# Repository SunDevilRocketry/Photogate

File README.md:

<h1>Photogate</h1>

<p>Current PCB Revision: 1.0</p>
<p>PCB Part Number: L0004</p>

<p>The photogate board functions as an optical sensor for calibrating the absolute position of stepper motors upon controller startup (L0005). The photogate is mounted on the stepper motor adjacent to the motor shaft, which is coupled to the stem of a ball-valve used as the main propellant valve in SDR's liquid engine. The photogate uses an infrared LED to produce an optical signal on the infrared-sensitive phototransistor surface. The board has a characteristic U-shape that allows a small standoff strut on the motor coupler to block the optical path of the sensor when the valve reaches the closed position. </p>

<p><b>Working Directory Structure:</b></p>

<p>
   doc: documentation
   
   src: source design files, e.g. schematic and PCB layout files

   lib: libraries for schematic symbols and footprints

   production: files needed for pcb fabrication, e.g. gerbers, profile, drill file

   sim: simulation models/files 

   cad: 3d models
  
   img: images of circuit/footprints for github display 
</p>

<h2>3D Model: </h2>

<h2>Schematic: </h2>

<h3>Power Supply </h3>

<h3>Emitter</h3>

<h3>Sensor</h3>

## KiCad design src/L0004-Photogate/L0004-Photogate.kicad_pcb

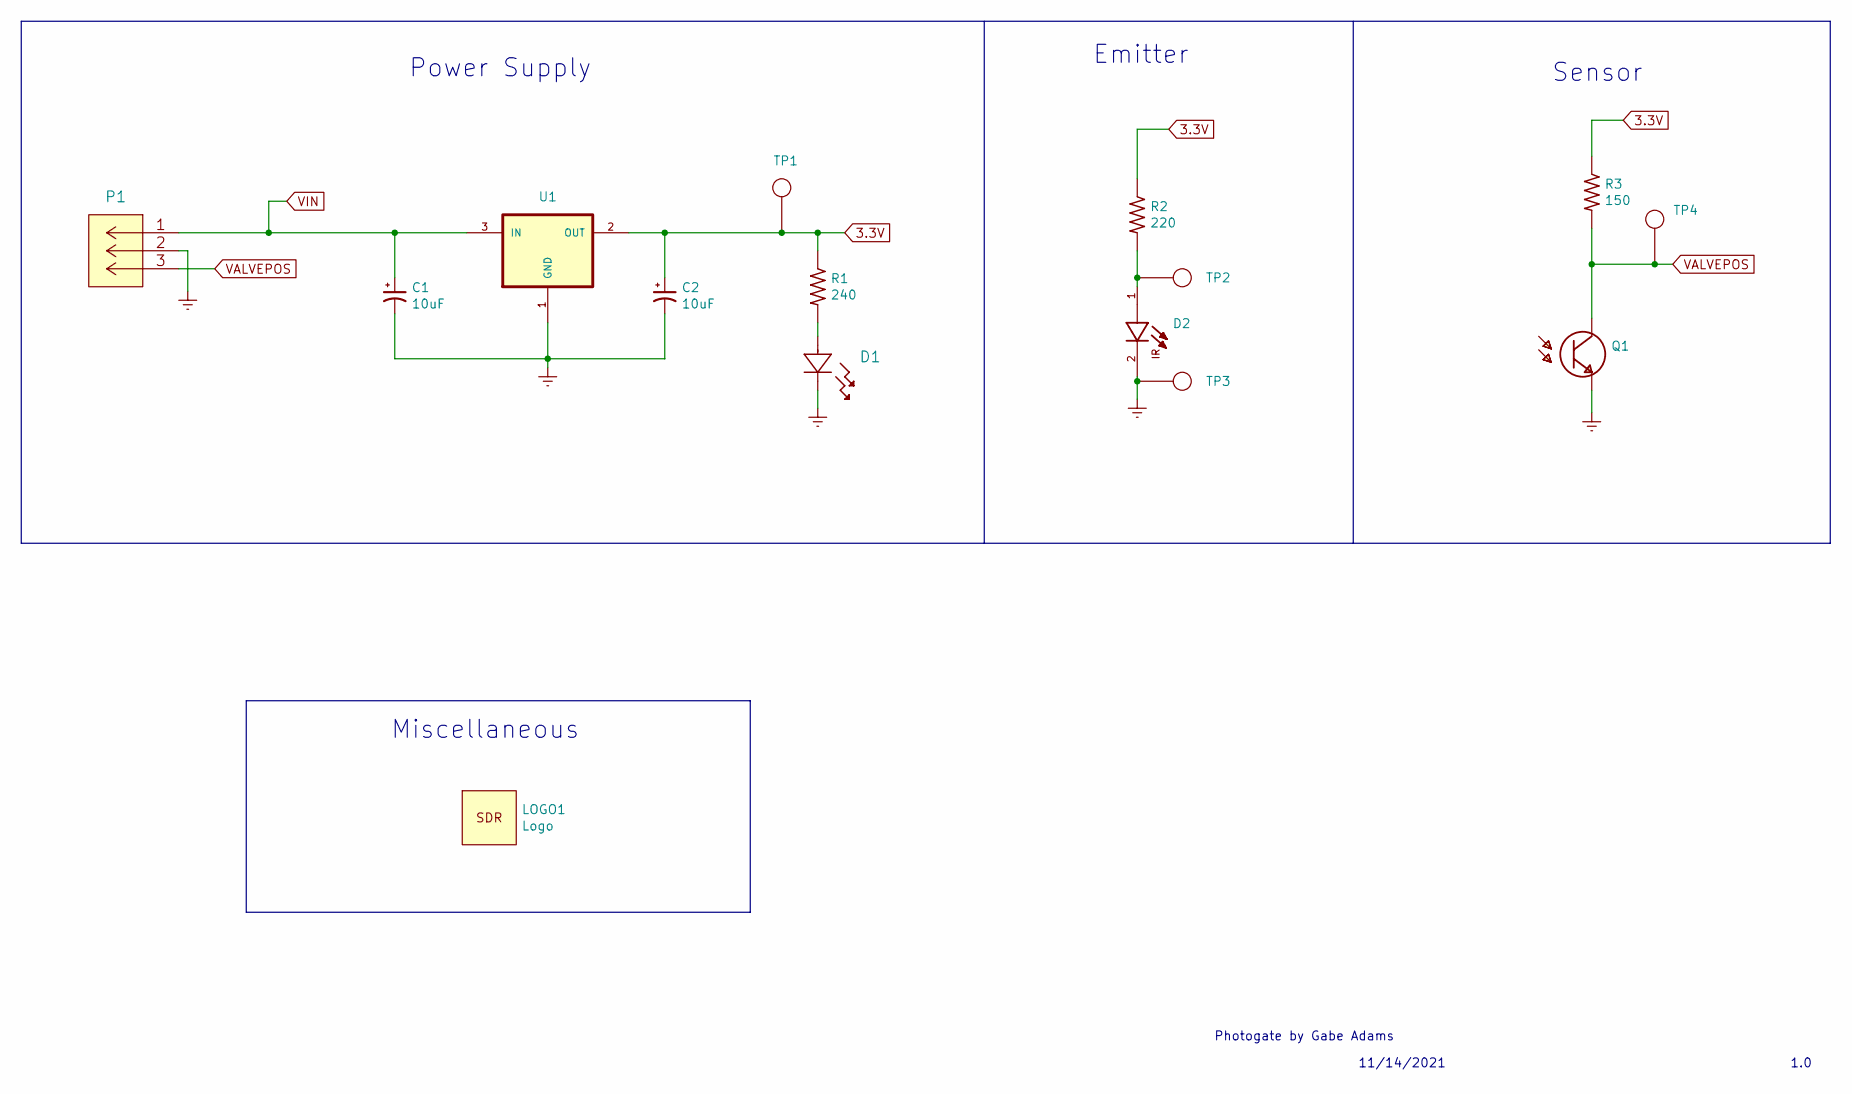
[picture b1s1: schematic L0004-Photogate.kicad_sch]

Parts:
C1, C2: 10uF; T491A106K010AT
D1: SML-LX1206GC-TR
D2: VSMY2853SL; DIO_VSMY2853SL
LOGO1: Logo
P1: 647676-3; CONN_2043-1X04G00DAU_OUP
Q1: SFH_3015_FA; XDCR_SFH_3015_FA
R1: 240; RES_0603
R2: 220; RES_0603
R3: 150; RES_0603
TP1, TP2, TP3, TP4: TP
U1: LMS8117AMP-3.3_NOPB; SOT230P700X180-4N

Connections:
3.3V: C2.1, R1.1, R2.1, R3.1, TP1.1, U1.2 (OUT)
Earth: C1.2, C2.2, D1.1, D2.2, P1.2, Q1.1, TP3.1, U1.1 (GND)
unnamed: D1.2, R1.2
unnamed: D2.1, R2.2, TP2.1
VALVEPOS: P1.3, Q1.2, R3.2, TP4.1
VIN: C1.1, P1.1, U1.3 (IN)

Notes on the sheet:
Power Supply
Photogate by Gabe Adams
Miscellaneous
1.0
Emitter
11/14/2021
Sensor

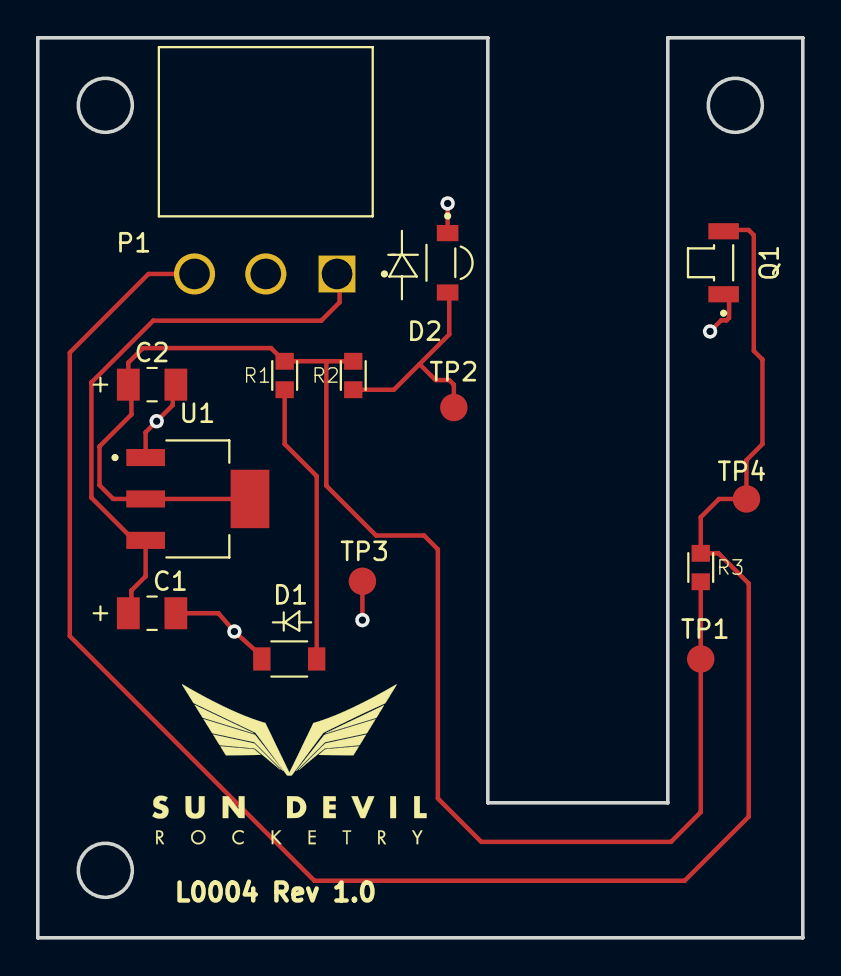
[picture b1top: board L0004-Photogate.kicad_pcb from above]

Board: 2 copper layers, 42.5 x 50.0 mm, 15 parts (0 on the bottom side), 6 nets.

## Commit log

2022-06-30 copied all files from old repository

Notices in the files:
parts and their libraries:
Copyright 2021 Accelerated Designs. All rights reserved.
